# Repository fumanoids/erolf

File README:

README FOR THE EROLF HARD- AND SOFTWARE RELEASE
            ===================================================

             2014-02-13 FUmanoids' Erolf Hardware Release v2014

          Copyright (c) 2014 FUmanoids / Freie Universität Berlin
                            All rights reserved

        For full license information, please refer to file LICENCE

Links:
       FUmanoids Homepage                           http://www.fumanoids.de
       FUmanoids on Facebook              http://www.facebook.com/fumanoids
       FUmanoids on Twitter                    http://twitter.com/fumanoids

       RoboCup Homepage                              http://www.robocup.org
       RoboCup Humanoid League Homepage          http://www.tzi.de/humanoid

This is part of the code/hardware release of team FUmanoids, version 2014. 

Our goal by releasing the source code and CAD files of components of our robot
is to provide some insight in humanoid soccer robot development, allowing other
teams to learn from our code and possibly our mistakes, but also to hopefully
encourage them to do the same and release their code as well. Though RoboCup is
a competition, it's also about research and finally to achieve our common goal -
to win against FIFA in 2050 ...

 1. PROJECT STRUCTURE
----------------------

The FUmanoids team has developed several software applications as well as our
own robots. The latter was developed internally and equipped with both
commercially available and self-built electronics.

This release addresses only the custom-built microcontroller board (named Erolf) 
used in the FUmanoid robots.

Neither a compiler, an SDK or CAD software is part of this package. In the
section "Getting Started" you find a list of recommended software to modify or
view the CAD files, to compile the software and to put the binaries onto the
processors.

 1.1 Overview of the package
-----------------------------

The project's root directory is "erolf" (the board's name).

The directories in the root directory are:

 - bin      -- some useful scripts and programs for building the program and
               documentation
 - build    -- All binary files of the program go here. This directory will
               be created during code compilation.
 - doc      -- The documentation directory. Here you can find some 
               documentation of the board. There are png files containing
               the schematics and the layout.
 - src      -- The actual source code.
               Note: The essential parts of the software is pretty well
               documented. Please consider this as a documentation 
               directory as well.
 - hardware -- Here you can find the CAD files for the PCB.

 2. THE EROLF PROJECT
------------------------- 

 2.1 Getting Started
-------------------------

 2.1.1 Software

The software is written in C with two extensions in assembler
(system_mutex_lock() and system_mutex_unlock()).

A compiler for the target hardware is not part of this package but can be picked
based on the user's preferences. We recommend using the arm-none-eabi-toolchain
(including gcc, ld and gdb) which can be found here:

                  https://launchpad.net/gcc-arm-embedded

 2.1.2 Hardware

To view the schematics and layout of this project we recommend using "CadSoft
EAGLE" which can be found at: http://www.cadsoftusa.com/

 2.1.3 Manufacturing

The PCB can be manufactured by most commonly known PCB services. A partlist can
be found in the folder where the schematics reside. But please double check the 
partlist since we cannot guarantee its completeness.

We chose every component on the board to be manually solderable. All you need is
a steady hand.

 2.1.4 Other Prerequisites
 
To flash the target a JTAG/SWD interface is needed.

We recommend using a "JLink" from Segger which supports JTAG and SWD for
flashing and debugging. Segger releases software acting as gdb-server and other
tools for common operating systems  (Linux, Mac, Windows). 

 2.2 Compiling the Software
---------------------------

The build system is based on premake 4. We include a more recent binary version
of premake4 than currently available in e.g. Ubuntu.. If you want the sourcecode
of premake have a look at http://industriousone.com/premake. Premake is licenced
under the terms of the BSD License.

The common IDE used for development in team FUmanoids is Eclipse/CDT which
is available at http://www.eclipse.org. Therefore we have the corresponding
project files added to our repository, to give an easy start. You can build the
code either by using Eclipse or by shell tools. Both ways are easy.
Other IDEs or editors can of course be used.

The build process generates two .elf files. One for each processor.

 2.2.1 Using Eclipse

If you choose to use Eclipse click File->Import and in the opening window
General->"Existing Project into Workspace" and choose the project's root
directory. Then you can compile the debug or release version of the software.

 2.2.2 Using the shell tools

You can simply run

 ./bin/compile.sh arm [release/debug]

to compile the code. This runs premake to generate the make-files and
runs "make" with the appropriate targets afterwards.

 2.3 Flashing the target
------------------------

In order to flash and debug the target software a JTAG/SWD Interface is needed.
Connect your debug interface to the processor you want to debug. For the pinning
information please consider looking in the schematics and the pinout information
of your JTAG/SWD interface.

In case you use a "JLink" from Segger start the JLinkGDBServer with the
parameter "-if swd" to use the Serial Wire Debug interface (similar to JTAG but
uses less wires). The output should tell you that a Cortex-M4 was identified.
If your debug interface cannot connect to the target doublecheck the power
supply and the pinning between your debug interface and the connector on
the PCB.

After your GDB-server is running you can use the flash.sh script (in the bin/
directory) to  flash the target. Use "./bin/flash.sh erolfP[1/2].elf".

In case you want to debug the software you can use the command line:

   run "arm-none-eabi-gdb"

In the following prompt enter:

   target remote localhost:2331
   monitor reset 0
   file erolfP[1/2].elf
   load
   monitor reset 0
   continue

In case you use Eclipse you can set up the "GDB Hardware Debugging" plugin for
this as well.

 4. REFERENCES
--------------

The framework used in this software was developed as part of the FUmanoid
project and is used in its power supply board as well (the project can be found
at http://www.fumanoids.de). The Berlin United Racing Team incorporates a
microcontroller board similar to the erolf which is operated by the framework as
well.

Many aspects of our work is described in the corresponding theses of our
students, which are available online at http://www.fumanoids.de/publications,
though most of them are in German.

This software uses libopencm3 which can be found at libopencm3.org.
Thank you very much for this project!

 5. CONTACT
-----------

We'd love to receive feedback, please feel free to contact us by email
at info@fumanoids.de. For information about our team and ongoing progress,
follow us on https://www.facebook.com/fumanoids, https://twitter.com/fumanoids
and http://www.fumanoids.de.

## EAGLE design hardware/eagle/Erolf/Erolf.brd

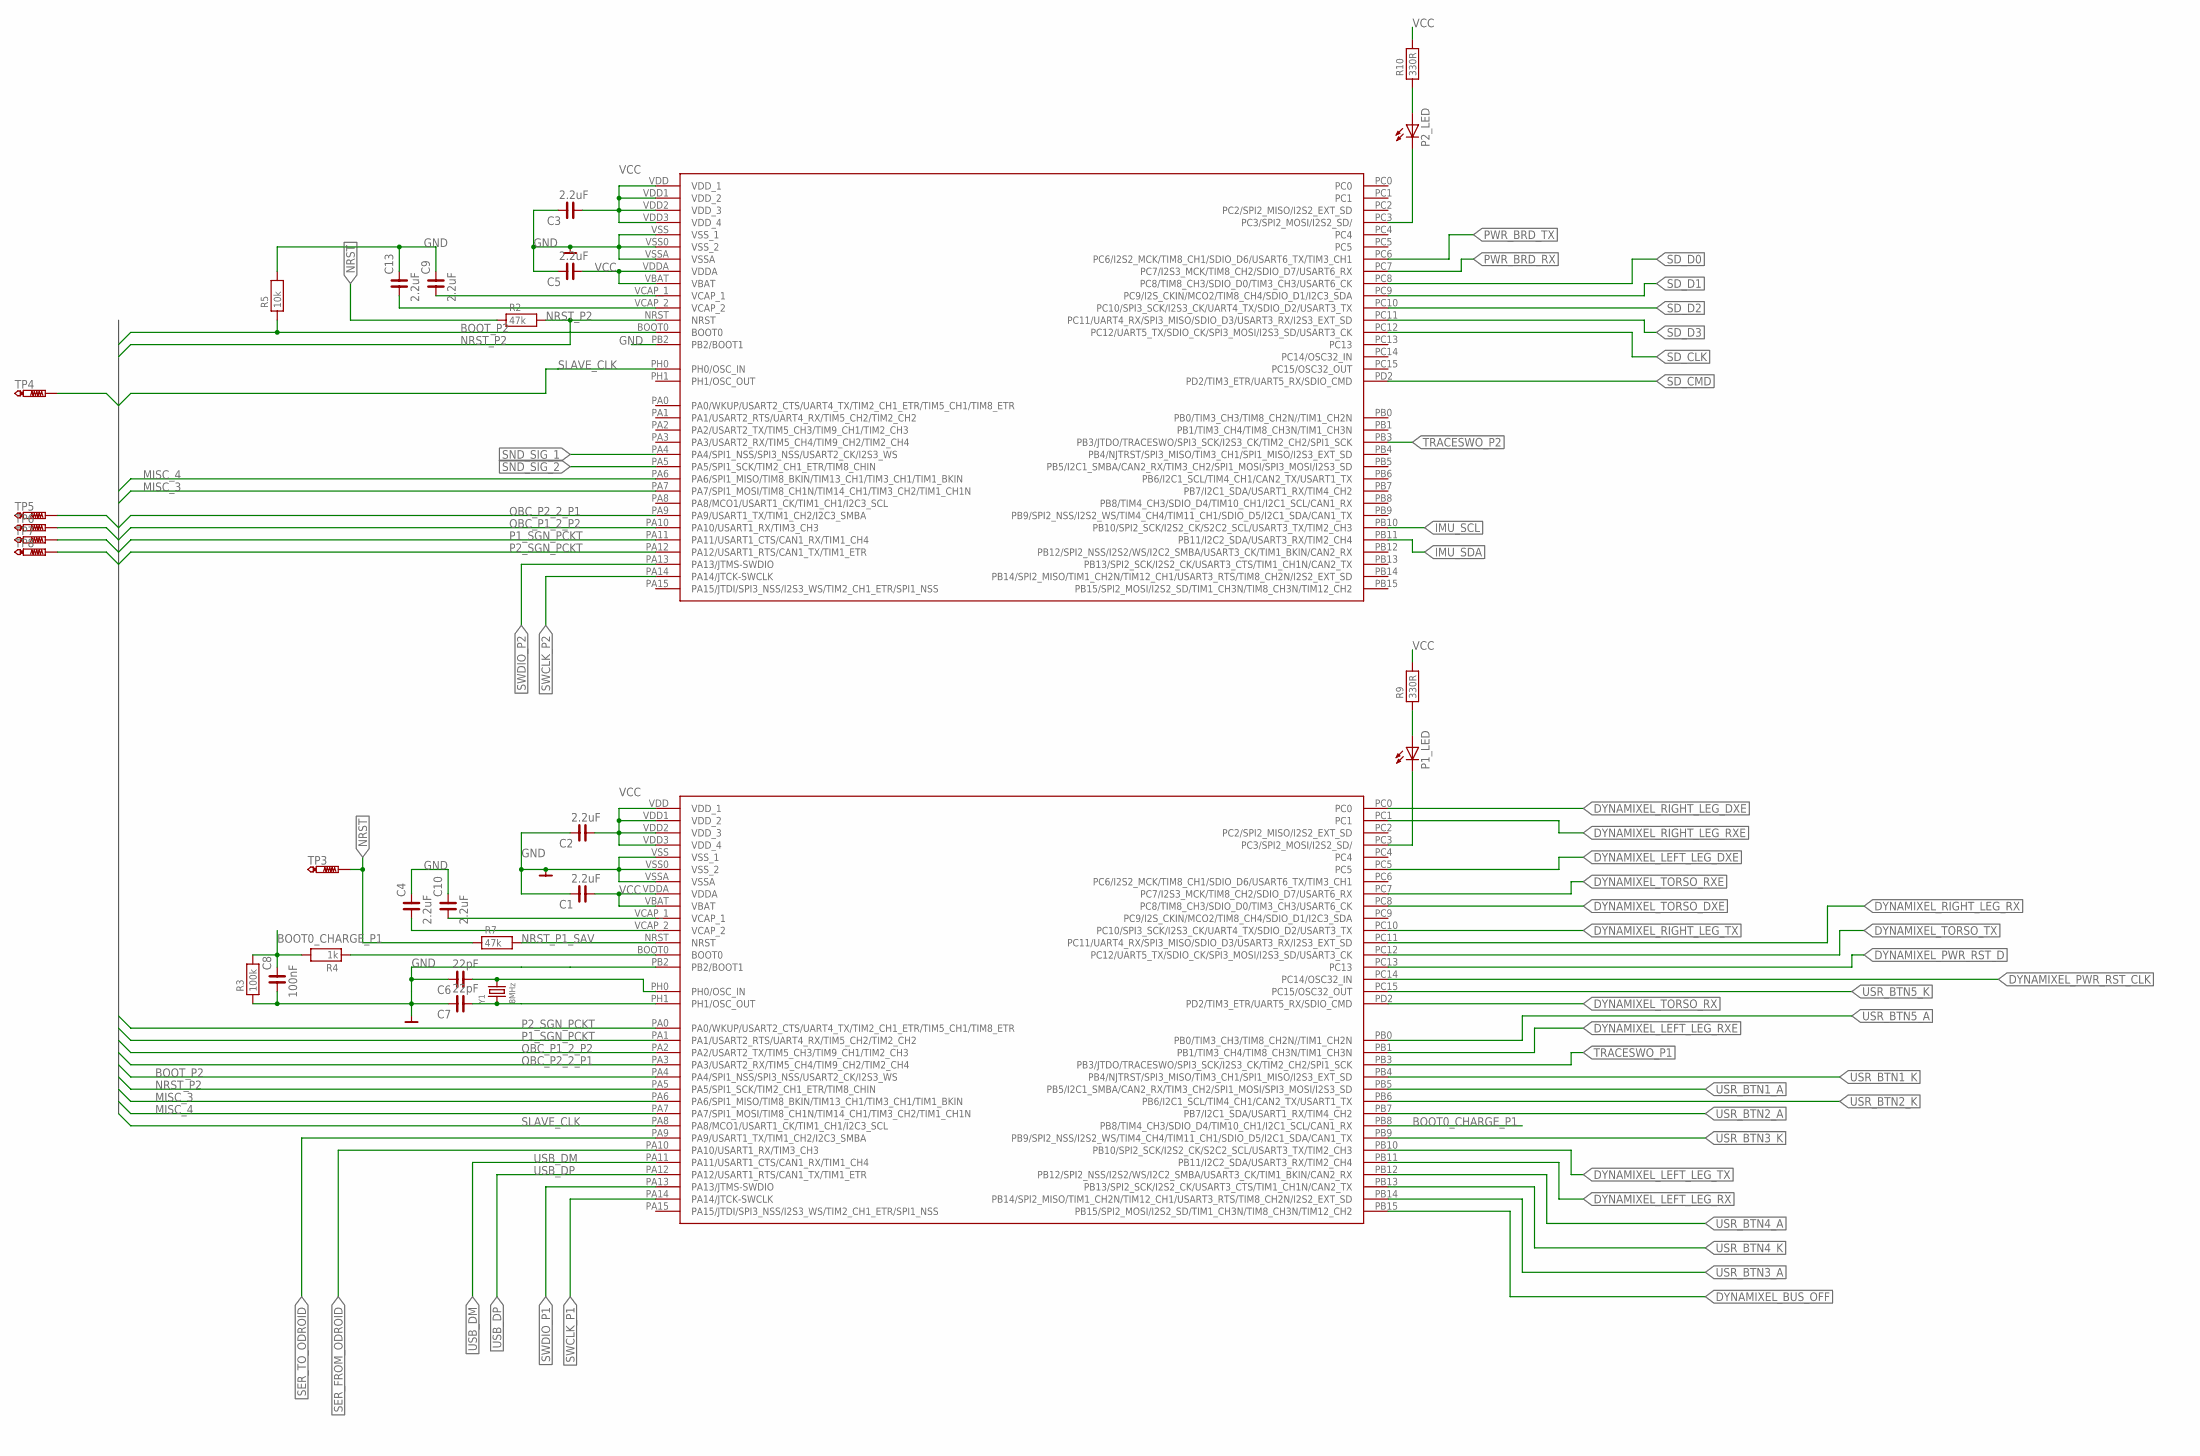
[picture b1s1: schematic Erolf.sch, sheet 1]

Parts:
C1, C2, C3, C4, C5, C9, C10, C13: 2.2uF; C0603
C6, C7: 22pF; C0603
C8: 100nF; C0603
P1_LED, P2_LED: LEDCHIP-LED0805; CHIP-LED0805
PROCESSOR_1, PROCESSOR_2: STM32-F405RB; LQFP-64
R2, R7: 47k; R0603
R3: 100k; R0603
R4: 1k; R0603
R5: 10k; R0603
R9, R10: 330R; R0603
TP3, TP4, TP5, TP6, TP7, TP8: PTR1TP06R; TP06R
Y1: 8MHz; CRYSTAL_4.9X1.8

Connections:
BOOT0_CHARGE_P1: C8.2, PROCESSOR_1.PB8 (PB8/TIM4_CH3/SDIO_D4/TIM10_CH1/I2C1_SCL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), R3.2, R4.2
BOOT_P2: PROCESSOR_1.PA4 (PA4/SPI1_NSS/SPI3_NSS/USART2_CK/I2S3_WS), PROCESSOR_2.BOOT0, R5.1
DYNAMIXEL_BUS_OFF: PROCESSOR_1.PB15 (PB15/SPI2_MOSI/I2S2_SD/TIM1_CH3N/TIM8_C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); also elsewhere on the board
DYNAMIXEL_LEFT_LEG_DXE: PROCESSOR_1.PC5; also elsewhere on the board
DYNAMIXEL_LEFT_LEG_RX: PROCESSOR_1.PB11 (PB11/I2C2_SDA/USART3_RX/TIM2_CH4); also elsewhere on the board
DYNAMIXEL_LEFT_LEG_RXE: PROCESSOR_1.PB1 (PB1/TIM3_CH4/TIM8_CH3N/TIM1_CH3N); also elsewhere on the board
DYNAMIXEL_LEFT_LEG_TX: PROCESSOR_1.PB10 (PB10/SPI2_SCK/I2S2_CK/S2C2_SCL/USART3_T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); also elsewhere on the board
DYNAMIXEL_PWR_RST_CLK: PROCESSOR_1.PC14 (PC14/OSC32_IN); also elsewhere on the board
DYNAMIXEL_PWR_RST_D: PROCESSOR_1.PC13; also elsewhere on the board
DYNAMIXEL_RIGHT_LEG_DXE: PROCESSOR_1.PC0; also elsewhere on the board
DYNAMIXEL_RIGHT_LEG_RX: PROCESSOR_1.PC11 (PC11/UART4_RX/SPI3_MISO/SDIO_D3/USART3_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); also elsewhere on the board
DYNAMIXEL_RIGHT_LEG_RXE: PROCESSOR_1.PC1; also elsewhere on the board
DYNAMIXEL_RIGHT_LEG_TX: PROCESSOR_1.PC10 (PC10/SPI3_SCK/I2S3_CK/UART4_TX/SDIO_D2/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); also elsewhere on the board
DYNAMIXEL_TORSO_DXE: PROCESSOR_1.PC8 (PC8/TIM8_CH3/SDIO_D0/TIM3_CH3/USART6_CK); also elsewhere on the board
DYNAMIXEL_TORSO_RX: PROCESSOR_1.PD2 (PD2/TIM3_ETR/UART5_RX/SDIO_CMD); also elsewhere on the board
DYNAMIXEL_TORSO_RXE: PROCESSOR_1.PC7 (PC7/I2S3_MCK/TIM8_CH2/SDIO_D7/USART6_RX); also elsewhere on the board
DYNAMIXEL_TORSO_TX: PROCESSOR_1.PC12 (PC12/UART5_TX/SDIO_CK/SPI3_MOSI/I2S3_SD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); also elsewhere on the board
GND: C1.2, C2.2, C3.2, C4.2, C5.2, C6.2, C7.2, C8.1, C9.2, C10.2, C13.2, PROCESSOR_1.PB2 (PB2/BOOT1), PROCESSOR_1.VSS (VSS_1), PROCESSOR_1.VSS0 (VSS_2), PROCESSOR_1.VSSA, PROCESSOR_2.PB2 (PB2/BOOT1), PROCESSOR_2.VSS (VSS_1), PROCESSOR_2.VSS0 (VSS_2), PROCESSOR_2.VSSA, R3.1, R5.2; also elsewhere on the board
IMU_SCL: PROCESSOR_2.PB10 (PB10/SPI2_SCK/I2S2_CK/S2C2_SCL/USART3_T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); also elsewhere on the board
IMU_SDA: PROCESSOR_2.PB11 (PB11/I2C2_SDA/USART3_RX/TIM2_CH4); also elsewhere on the board
MISC_3: PROCESSOR_1.PA6 (PA6/SPI1_MISO/TIM8_BKIN/TIM13_CH1/TIM3_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), PROCESSOR_2.PA7 (PA7/SPI1_MOSI/TIM8_CH1N/TIM14_CH1/TIM3_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)
MISC_4: PROCESSOR_1.PA7 (PA7/SPI1_MOSI/TIM8_CH1N/TIM14_CH1/TIM3_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), PROCESSOR_2.PA6 (PA6/SPI1_MISO/TIM8_BKIN/TIM13_CH1/TIM3_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)
unnamed: C10.1, PROCESSOR_1.VCAP_1
unnamed: P1_LED.A, R9.1
unnamed: P2_LED.A, R10.1
unnamed: P1_LED.C, PROCESSOR_1.PC3 (PC3/SPI2_MOSI/I2S2_SD/)
unnamed: C13.1, PROCESSOR_2.VCAP_2
unnamed: C9.1, PROCESSOR_2.VCAP_1
unnamed: PROCESSOR_1.BOOT0, R4.1
unnamed: P2_LED.C, PROCESSOR_2.PC3 (PC3/SPI2_MOSI/I2S2_SD/)
unnamed: C4.1, PROCESSOR_1.VCAP_2
NRST: R2.1, R7.1, TP3.TP; also elsewhere on the board
NRST_P1_SAV: PROCESSOR_1.NRST, R7.2
NRST_P2: PROCESSOR_1.PA5 (PA5/SPI1_SCK/TIM2_CH1_ETR/TIM8_CHIN), PROCESSOR_2.NRST, R2.2
OBC_P1_2_P2: PROCESSOR_1.PA2 (PA2/USART2_TX/TIM5_CH3/TIM9_CH1/TIM2_CH3), PROCESSOR_2.PA10 (PA10/USART1_RX/TIM3_CH3), TP6.TP
OBC_P2_2_P1: PROCESSOR_1.PA3 (PA3/USART2_RX/TIM5_CH4/TIM9_CH2/TIM2_CH4), PROCESSOR_2.PA9 (PA9/USART1_TX/TIM1_CH2/I2C3_SMBA), TP5.TP
OSC_IN: C6.1, PROCESSOR_1.PH0 (PH0/OSC_IN), Y1.2
OSC_OUT: C7.1, PROCESSOR_1.PH1 (PH1/OSC_OUT), Y1.1
P1_SGN_PCKT: PROCESSOR_1.PA1 (PA1/USART2_RTS/UART4_RX/TIM5_CH2/TIM2_C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), PROCESSOR_2.PA11 (PA11/USART1_CTS/CAN1_RX/TIM1_CH4), TP7.TP
P2_SGN_PCKT: PROCESSOR_1.PA0 (PA0/WKUP/USART2_CTS/UART4_TX/TIM2_CH1_E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), PROCESSOR_2.PA12 (PA12/USART1_RTS/CAN1_TX/TIM1_ETR), TP8.TP
PWR_BRD_RX: PROCESSOR_2.PC7 (PC7/I2S3_MCK/TIM8_CH2/SDIO_D7/USART6_RX); also elsewhere on the board
PWR_BRD_TX: PROCESSOR_2.PC6 (PC6/I2S2_MCK/TIM8_CH1/SDIO_D6/USART6_TX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); also elsewhere on the board
SD_CLK: PROCESSOR_2.PC12 (PC12/UART5_TX/SDIO_CK/SPI3_MOSI/I2S3_SD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); also elsewhere on the board
SD_CMD: PROCESSOR_2.PD2 (PD2/TIM3_ETR/UART5_RX/SDIO_CMD); also elsewhere on the board
SD_D0: PROCESSOR_2.PC8 (PC8/TIM8_CH3/SDIO_D0/TIM3_CH3/USART6_CK); also elsewhere on the board
SD_D1: PROCESSOR_2.PC9 (PC9/I2S_CKIN/MCO2/TIM8_CH4/SDIO_D1/I2C3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); also elsewhere on the board
SD_D2: PROCESSOR_2.PC10 (PC10/SPI3_SCK/I2S3_CK/UART4_TX/SDIO_D2/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); also elsewhere on the board
SD_D3: PROCESSOR_2.PC11 (PC11/UART4_RX/SPI3_MISO/SDIO_D3/USART3_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); also elsewhere on the board
SER_FROM_ODROID: PROCESSOR_1.PA10 (PA10/USART1_RX/TIM3_CH3); also elsewhere on the board
SER_TO_ODROID: PROCESSOR_1.PA9 (PA9/USART1_TX/TIM1_CH2/I2C3_SMBA); also elsewhere on the board
SLAVE_CLK: PROCESSOR_1.PA8 (PA8/MCO1/USART1_CK/TIM1_CH1/I2C3_SCL), PROCESSOR_2.PH0 (PH0/OSC_IN), TP4.TP
SND_SIG_1: PROCESSOR_2.PA4 (PA4/SPI1_NSS/SPI3_NSS/USART2_CK/I2S3_WS); also elsewhere on the board
SND_SIG_2: PROCESSOR_2.PA5 (PA5/SPI1_SCK/TIM2_CH1_ETR/TIM8_CHIN); also elsewhere on the board
SWCLK_P1: PROCESSOR_1.PA14 (PA14/JTCK-SWCLK); also elsewhere on the board
SWCLK_P2: PROCESSOR_2.PA14 (PA14/JTCK-SWCLK); also elsewhere on the board
SWDIO_P1: PROCESSOR_1.PA13 (PA13/JTMS-SWDIO); also elsewhere on the board
SWDIO_P2: PROCESSOR_2.PA13 (PA13/JTMS-SWDIO); also elsewhere on the board
TRACESWO_P1: PROCESSOR_1.PB3 (PB3/JTDO/TRACESWO/SPI3_SCK/I2S3_CK/TIM2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); also elsewhere on the board
TRACESWO_P2: PROCESSOR_2.PB3 (PB3/JTDO/TRACESWO/SPI3_SCK/I2S3_CK/TIM2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); also elsewhere on the board
USB_DM: PROCESSOR_1.PA11 (PA11/USART1_CTS/CAN1_RX/TIM1_CH4); also elsewhere on the board
USB_DP: PROCESSOR_1.PA12 (PA12/USART1_RTS/CAN1_TX/TIM1_ETR); also elsewhere on the board
USR_BTN1_A: PROCESSOR_1.PB5 (PB5/I2C1_SMBA/CAN2_RX/TIM3_CH2/SPI1_MOS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); also elsewhere on the board
USR_BTN1_K: PROCESSOR_1.PB4 (PB4/NJTRST/SPI3_MISO/TIM3_CH1/SPI1_MISO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); also elsewhere on the board
USR_BTN2_A: PROCESSOR_1.PB7 (PB7/I2C1_SDA/USART1_RX/TIM4_CH2); also elsewhere on the board
USR_BTN2_K: PROCESSOR_1.PB6 (PB6/I2C1_SCL/TIM4_CH1/CAN2_TX/USART1_TX); also elsewhere on the board
USR_BTN3_A: PROCESSOR_1.PB14 (PB14/SPI2_MISO/TIM1_CH2N/TIM12_CH1/USAR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); also elsewhere on the board
USR_BTN3_K: PROCESSOR_1.PB9 (PB9/SPI2_NSS/I2S2_WS/TIM4_CH4/TIM11_CH1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); also elsewhere on the board
USR_BTN4_A: PROCESSOR_1.PB12 (PB12/SPI2_NSS/I2S2/WS/I2C2_SMBA/USART3_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); also elsewhere on the board
USR_BTN4_K: PROCESSOR_1.PB13 (PB13/SPI2_SCK/I2S2_CK/USART3_CTS/TIM1_C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); also elsewhere on the board
USR_BTN5_A: PROCESSOR_1.PB0 (PB0/TIM3_CH3/TIM8_CH2N//TIM1_CH2N); also elsewhere on the board
USR_BTN5_K: PROCESSOR_1.PC15 (PC15/OSC32_OUT); also elsewhere on the board
VCC: C1.1, C2.1, C3.1, C5.1, PROCESSOR_1.VBAT, PROCESSOR_1.VDD (VDD_1), PROCESSOR_1.VDD1 (VDD_2), PROCESSOR_1.VDD2 (VDD_3), PROCESSOR_1.VDD3 (VDD_4), PROCESSOR_1.VDDA, PROCESSOR_2.VBAT, PROCESSOR_2.VDD (VDD_1), PROCESSOR_2.VDD1 (VDD_2), PROCESSOR_2.VDD2 (VDD_3), PROCESSOR_2.VDD3 (VDD_4), PROCESSOR_2.VDDA, R9.2, R10.2; also elsewhere on the board

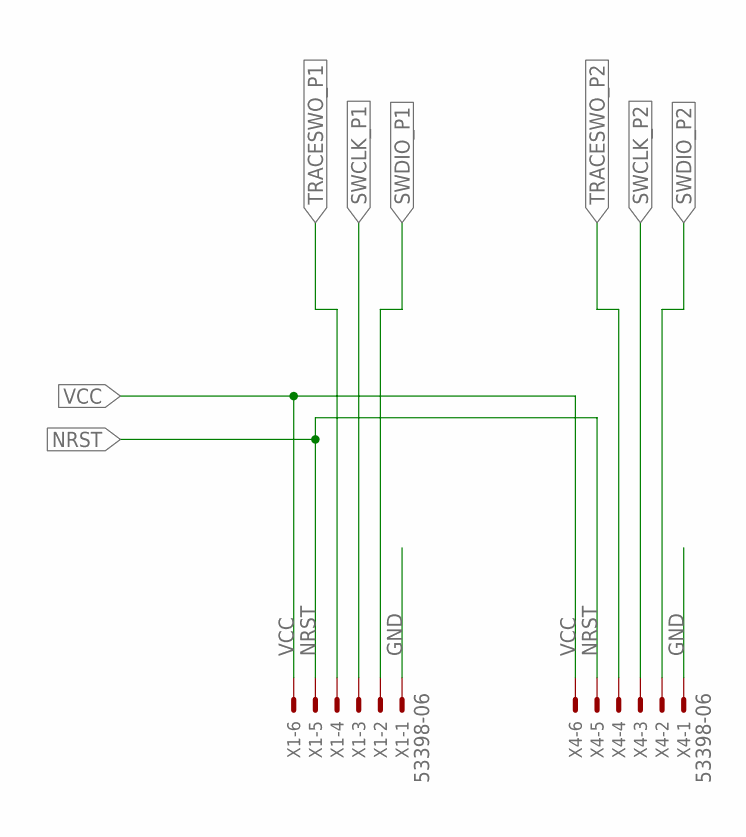
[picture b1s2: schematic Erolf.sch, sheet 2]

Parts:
X1, X4: 53398-06

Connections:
GND: X1.1, X4.1; also elsewhere on the board
NRST: X1.5, X4.5; also elsewhere on the board
SWCLK_P1: X1.3; also elsewhere on the board
SWCLK_P2: X4.3; also elsewhere on the board
SWDIO_P1: X1.2; also elsewhere on the board
SWDIO_P2: X4.2; also elsewhere on the board
TRACESWO_P1: X1.4; also elsewhere on the board
TRACESWO_P2: X4.4; also elsewhere on the board
VCC: X1.6, X4.6; also elsewhere on the board

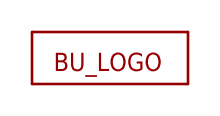
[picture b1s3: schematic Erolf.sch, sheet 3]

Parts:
U$8: LOGO

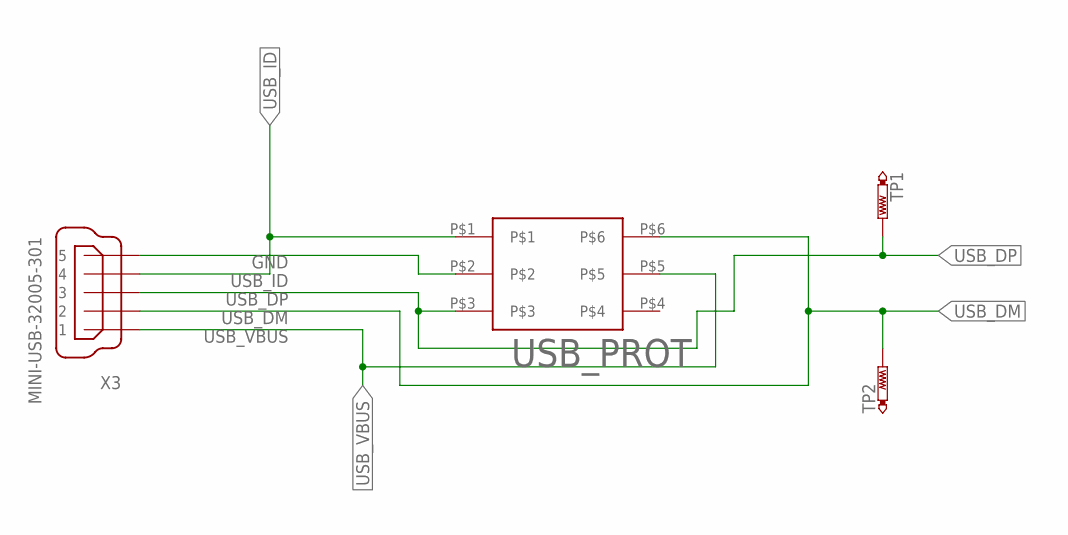
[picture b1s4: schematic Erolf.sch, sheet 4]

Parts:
TP1, TP2: PTR1TP06R; TP06R
USB_PROT: VBUS054B; LLP75-6L; DIGIKEY 751-1453-1-ND
X3: MINI-USB-32005-301; 32005-301

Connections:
GND: USB_PROT.P$2, X3.5; also elsewhere on the board
USB_DM: TP2.TP, USB_PROT.P$6, X3.2; also elsewhere on the board
USB_DP: TP1.TP, USB_PROT.P$3, X3.3; also elsewhere on the board
USB_ID: USB_PROT.P$1, X3.4
USB_VBUS: USB_PROT.P$5, X3.1

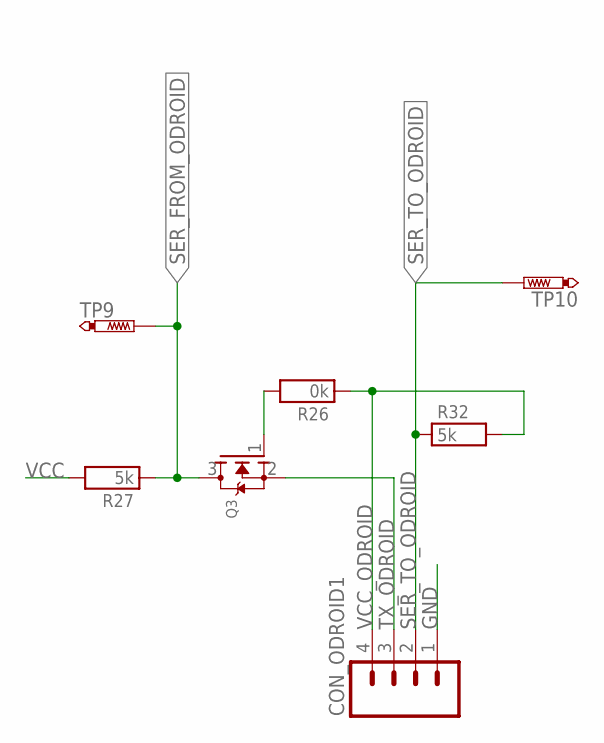
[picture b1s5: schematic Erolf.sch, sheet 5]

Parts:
CON_ODROID1: M04; 04P
Q3: MOSFET-NREFLOW; SOT23
R26: 0k; R0603
R27, R32: 5k; R0603
TP9, TP10: PTR1TP06R; TP06R

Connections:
GND: CON_ODROID1.1; also elsewhere on the board
unnamed: Q3.1 (G), R26.2
SER_FROM_ODROID: Q3.3 (D), R27.1, TP9.TP; also elsewhere on the board
SER_TO_ODROID: CON_ODROID1.2, R32.1, TP10.TP; also elsewhere on the board
TX_ODROID: CON_ODROID1.3, Q3.2 (S)
VCC: R27.2; also elsewhere on the board
VCC_ODROID: CON_ODROID1.4, R26.1, R32.2

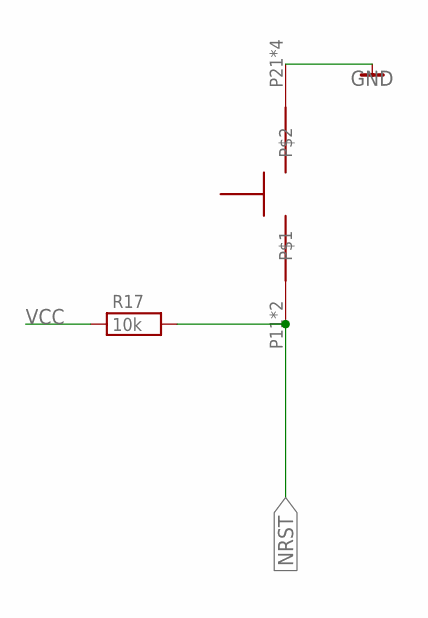
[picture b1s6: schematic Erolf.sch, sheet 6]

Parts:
R17: 10k; R0603
U$3: BUTTON

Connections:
GND: U$3.P21, U$3.P22, U$3.P23, U$3.P24; also elsewhere on the board
NRST: R17.2, U$3.P11, U$3.P12; also elsewhere on the board
VCC: R17.1; also elsewhere on the board

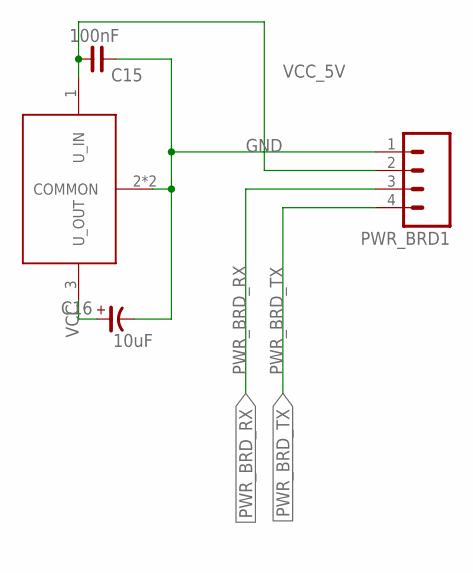
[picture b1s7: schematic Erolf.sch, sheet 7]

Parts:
BLUBB: UA78M00; SOT223-4
C15: 100nF; C0603
C16: 10uF; CE-025X060
PWR_BRD1: M04; 04P

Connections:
GND: BLUBB.2 (COMMON), BLUBB.4 (COMMON), C15.2, C16.-, PWR_BRD1.1; also elsewhere on the board
PWR_BRD_RX: PWR_BRD1.3; also elsewhere on the board
PWR_BRD_TX: PWR_BRD1.4; also elsewhere on the board
VCC: BLUBB.3 (U_OUT), C16.+; also elsewhere on the board
VCC_5V: BLUBB.1 (U_IN), C15.1, PWR_BRD1.2; also elsewhere on the board

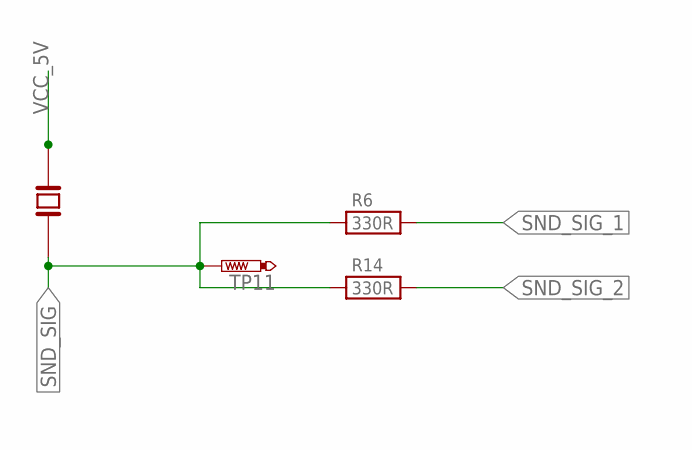
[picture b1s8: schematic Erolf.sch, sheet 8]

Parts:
R6, R14: 330R; R0603
TP11: PTR1TP06R; TP06R
U$1: PS1240P02CT3

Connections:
SND_SIG: R6.1, R14.1, TP11.TP, U$1.P$2
SND_SIG_1: R6.2; also elsewhere on the board
SND_SIG_2: R14.2; also elsewhere on the board
VCC_5V: U$1.P$1; also elsewhere on the board

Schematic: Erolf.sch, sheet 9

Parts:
U$4: MINI-IMU-9V2; PCB

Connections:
GND: U$4.GND; also elsewhere on the board
IMU_SCL: U$4.SCL; also elsewhere on the board
IMU_SDA: U$4.SDA; also elsewhere on the board
VCC: U$4.VDD, U$4.VIN; also elsewhere on the board

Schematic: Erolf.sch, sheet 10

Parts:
C17: 100nF; C0603
R16: 33kR; R0603
RN1: 33kR; EXBS8V
U$2: MICROSD

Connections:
GND: C17.2, U$2.6 (VSS), U$2.MT1 (GND), U$2.MT2 (GND1); also elsewhere on the board
SD_CLK: RN1.6 (2), U$2.5 (SCLK); also elsewhere on the board
SD_CMD: U$2.3 (DATA_IN); also elsewhere on the board
SD_D0: RN1.7 (2), U$2.7 (DATA_OUT); also elsewhere on the board
SD_D1: RN1.8 (2), U$2.8 (DAT1); also elsewhere on the board
SD_D2: R16.1, U$2.1 (DAT2); also elsewhere on the board
SD_D3: RN1.5 (2), U$2.2 (CS); also elsewhere on the board
VCC: C17.1, R16.2, RN1.1, RN1.2 (1), RN1.3 (1), RN1.4 (1), U$2.4 (VDD); also elsewhere on the board

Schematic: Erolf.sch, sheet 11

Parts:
R1, R8, R11, R12, R33: 330R; R0603
R34, R35, R36, R37, R38: 10kR; R0603
X2: 53261-10

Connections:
USR_BTN1_A: R38.2, X2.9; also elsewhere on the board
USR_BTN1_K: R33.1, X2.10; also elsewhere on the board
USR_BTN2_A: R37.2, X2.7; also elsewhere on the board
USR_BTN2_K: R12.1, X2.8; also elsewhere on the board
USR_BTN3_A: R36.2, X2.5; also elsewhere on the board
USR_BTN3_K: R11.1, X2.6; also elsewhere on the board
USR_BTN4_A: R35.2, X2.3; also elsewhere on the board
USR_BTN4_K: R8.1, X2.4; also elsewhere on the board
USR_BTN5_A: R34.2, X2.1; also elsewhere on the board
USR_BTN5_K: R1.1, X2.2; also elsewhere on the board
VCC: R1.2, R8.2, R11.2, R12.2, R33.2, R34.1, R35.1, R36.1, R37.1, R38.1; also elsewhere on the board

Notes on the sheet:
when using buttons with embedded LED connect the LED's anode with one pin of the button and the LED's cathode with the other pin of the button. The LED's anode shall be connected to USR_BTNx_A and the cathode to USR_BTNx_K

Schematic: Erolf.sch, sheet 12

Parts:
DYNAMIXEL_LEFT_LEG: M04; 04P
DYNAMIXEL_RIGHT_LEG: M04; 04P
DYNAMIXEL_TORSO: M04; 04P
IC2, IC12, IC13: MAX481CSA; SO08
RN4, RN5, RN6: 10k; EXBV4V

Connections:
DYNAMIXEL_LEFT_LEG_A: DYNAMIXEL_LEFT_LEG.2, IC2.6 (A); also elsewhere on the board
DYNAMIXEL_LEFT_LEG_B: DYNAMIXEL_LEFT_LEG.1, IC2.7 (B), RN4.1, RN4.2 (1); also elsewhere on the board
DYNAMIXEL_LEFT_LEG_DXE: IC2.3 (DE); also elsewhere on the board
DYNAMIXEL_LEFT_LEG_RX: IC2.1 (RO); also elsewhere on the board
DYNAMIXEL_LEFT_LEG_RXE: IC2.2 (RE/); also elsewhere on the board
DYNAMIXEL_LEFT_LEG_TX: IC2.4 (DI); also elsewhere on the board
DYNAMIXEL_RIGHT_LEG_A: DYNAMIXEL_RIGHT_LEG.2, IC12.6 (A); also elsewhere on the board
DYNAMIXEL_RIGHT_LEG_B: DYNAMIXEL_RIGHT_LEG.1, IC12.7 (B), RN5.1, RN5.2 (1); also elsewhere on the board
DYNAMIXEL_RIGHT_LEG_DXE: IC12.3 (DE); also elsewhere on the board
DYNAMIXEL_RIGHT_LEG_RX: IC12.1 (RO); also elsewhere on the board
DYNAMIXEL_RIGHT_LEG_RXE: IC12.2 (RE/); also elsewhere on the board
DYNAMIXEL_RIGHT_LEG_TX: IC12.4 (DI); also elsewhere on the board
DYNAMIXEL_TORSO_A: DYNAMIXEL_TORSO.2, IC13.6 (A); also elsewhere on the board
DYNAMIXEL_TORSO_B: DYNAMIXEL_TORSO.1, IC13.7 (B), RN6.1, RN6.2 (1); also elsewhere on the board
DYNAMIXEL_TORSO_DXE: IC13.3 (DE); also elsewhere on the board
DYNAMIXEL_TORSO_RX: IC13.1 (RO); also elsewhere on the board
DYNAMIXEL_TORSO_RXE: IC13.2 (RE/); also elsewhere on the board
DYNAMIXEL_TORSO_TX: IC13.4 (DI); also elsewhere on the board
GND: DYNAMIXEL_LEFT_LEG.4, DYNAMIXEL_RIGHT_LEG.4, DYNAMIXEL_TORSO.4, IC2.5 (GND), IC12.5 (GND), IC13.5 (GND), RN4.3 (2), RN5.3 (2), RN6.3 (2); also elsewhere on the board
VCC: IC2.8 (VCC), IC12.8 (VCC), IC13.8 (VCC), RN4.4 (2), RN5.4 (2), RN6.4 (2); also elsewhere on the board
VCC_BAT: DYNAMIXEL_LEFT_LEG.3, DYNAMIXEL_RIGHT_LEG.3, DYNAMIXEL_TORSO.3; also elsewhere on the board

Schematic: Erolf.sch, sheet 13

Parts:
C11: 100nF; C0603
D1: ZENER-DIODESOD80C; SOD80C
D2: DIODE-MICROMELF-R; MICROMELF-R
DYNAMIXEL_PWR: M04; 04P
IC1, IC3, IC4, IC5, IC6, IC7: TL331; DBV-R-PDSO-G5
Q1: BSS123; SOT23
R13, R18, R23: 10kR; R0603
R15: 1kR; R0603
TP20, TP21, TP22: PTR1TP06R; TP06R
U$6: SI4459ADY; SO-8
U$7: SN74LVC1G175; DCV_R-PDSO-6

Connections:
DYNAMIXEL_BUS_OFF: Q1.1 (G), R15.2; also elsewhere on the board
DYNAMIXEL_BUS_OFF_AUTO_TRIG: IC1.4 (OUT), IC3.4 (OUT), IC4.4 (OUT), IC5.4 (OUT), IC6.4 (OUT), IC7.4 (OUT), R23.2, TP20.TP, U$7.P$6 (NCLR)
DYNAMIXEL_LEFT_LEG_A: IC5.1 (-IN); also elsewhere on the board
DYNAMIXEL_LEFT_LEG_B: IC6.1 (-IN); also elsewhere on the board
DYNAMIXEL_PWR_RST_CLK: U$7.P$1 (CLK); also elsewhere on the board
DYNAMIXEL_PWR_RST_D: U$7.P$3 (D); also elsewhere on the board
DYNAMIXEL_RIGHT_LEG_A: IC4.1 (-IN); also elsewhere on the board
DYNAMIXEL_RIGHT_LEG_B: IC3.1 (-IN); also elsewhere on the board
DYNAMIXEL_TORSO_A: DYNAMIXEL_PWR.2, IC7.1 (-IN); also elsewhere on the board
DYNAMIXEL_TORSO_B: DYNAMIXEL_PWR.1, IC1.1 (-IN); also elsewhere on the board
GND: C11.2, D1.A, DYNAMIXEL_PWR.4, IC1.2 (GND), IC3.2 (GND), IC4.2 (GND), IC5.2 (GND), IC6.2 (GND), IC7.2 (GND), Q1.2 (S), U$7.P$2 (GND); also elsewhere on the board
unnamed: R15.1, U$7.P$4 (Q)
unnamed: Q1.3 (D), R13.1, U$6.P4 (G)
unnamed: D2.C, R18.1
VCC: R23.1, U$7.P$5 (VCC); also elsewhere on the board
VCC_BAT: TP22.TP, U$6.P5 (D), U$6.P6 (D), U$6.P7 (D), U$6.P8 (D); also elsewhere on the board
VCC_BAT_PRE: D2.A, DYNAMIXEL_PWR.3, IC1.5 (V+), IC3.5 (V+), IC4.5 (V+), IC5.5 (V+), IC6.5 (V+), IC7.5 (V+), R13.2, U$6.P1 (S), U$6.P2 (S), U$6.P3 (S)
V_SAFETY_REF: C11.1, D1.C, IC1.3 (+IN), IC3.3 (+IN), IC4.3 (+IN), IC5.3 (+IN), IC6.3 (+IN), IC7.3 (+IN), R18.2, TP21.TP

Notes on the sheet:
the recommended value of this Z-Diode is about the maximum allowed voltage of the RS485 transceivers (usually 12V) minus some margin (2V suffice) 10 Volts is usually a good measure

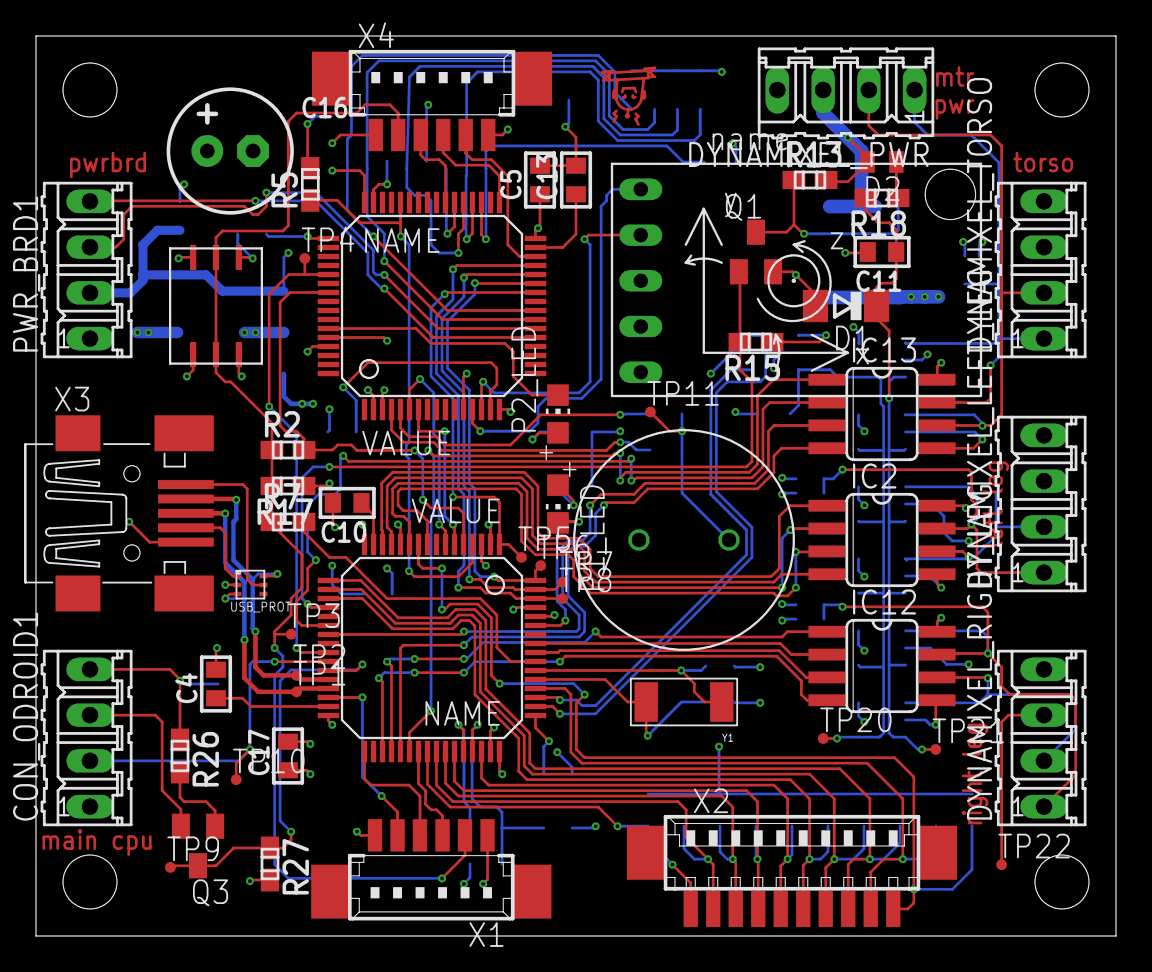
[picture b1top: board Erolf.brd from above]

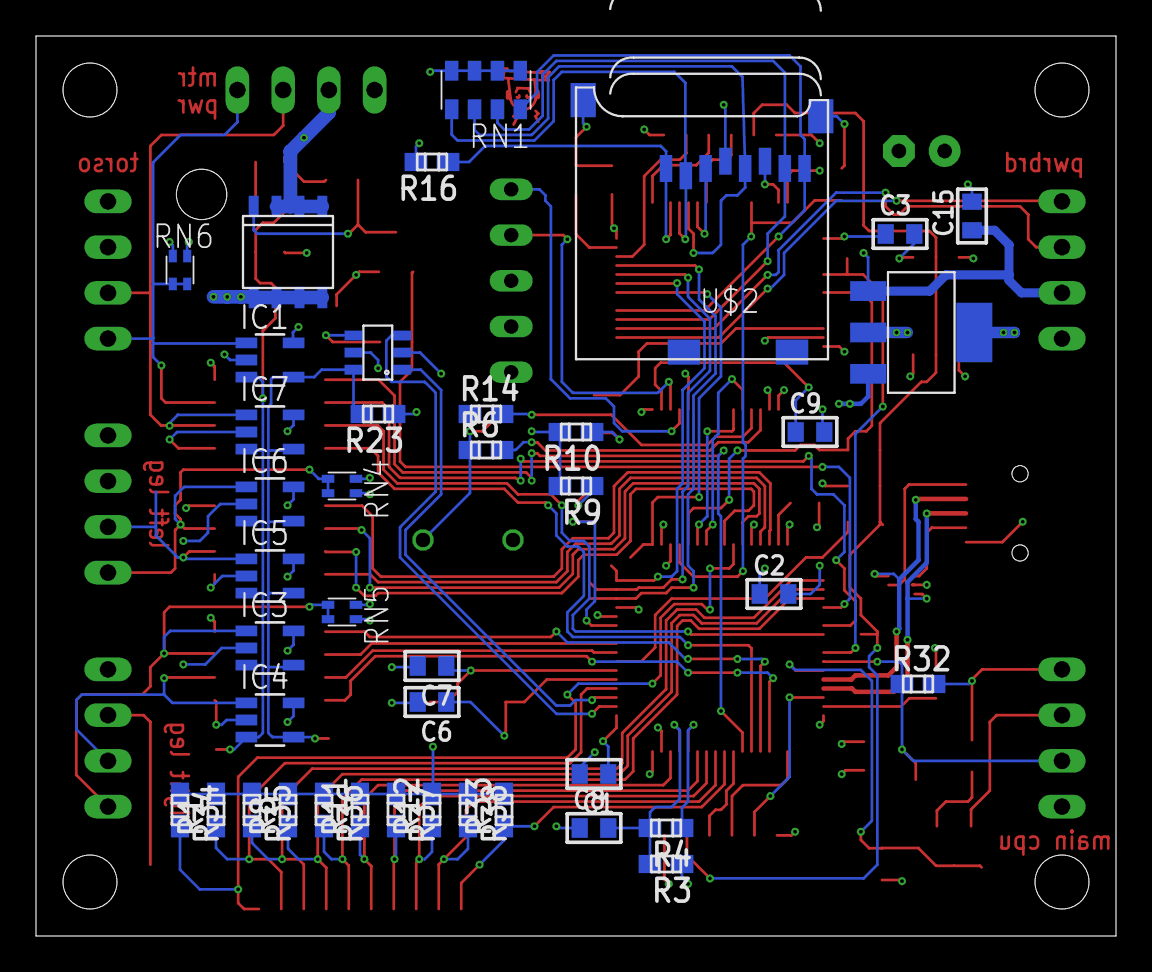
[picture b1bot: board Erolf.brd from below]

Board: 4 copper layers, 60.0 x 50.0 mm, 98 parts (41 on the bottom side), 92 nets.

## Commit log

2014-02-13 code release 2014

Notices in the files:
parts and their libraries:
rc-master: Copyright (C) 2007, Bob Starr
